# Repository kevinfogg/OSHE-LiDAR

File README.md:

# OSHE-LiDAR
This is the Open Source Hardware Enterprise (OSHE) LiDAR Bot repository at MTU

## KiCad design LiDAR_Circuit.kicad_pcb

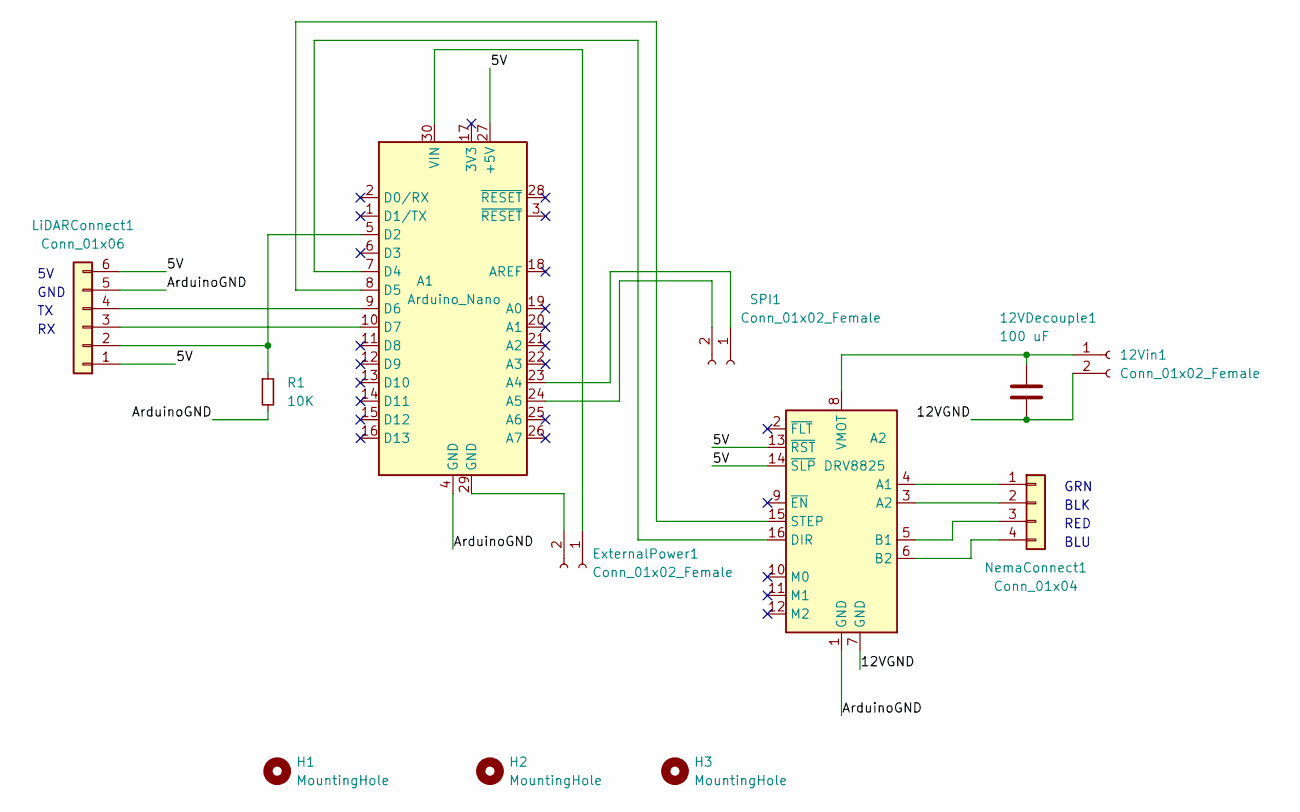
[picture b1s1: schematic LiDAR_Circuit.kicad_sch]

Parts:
12VDecouple1: 100 uF; CP_Radial_D6.3mm_P2.50mm
12Vin1: Conn_01x02_Female; TerminalBlock_Altech_AK300-2_P5.00mm
A1: Arduino_Nano
A2: DRV8825; Pololu_Breakout-16_15.2x20.3mm
ExternalPower1: Conn_01x02_Female; PinHeader_1x02_P2.54mm_Horizontal
H1, H2, H3: MountingHole; MountingHole_3.2mm_M3
LiDARConnect1: Conn_01x06; PinSocket_1x06_P2.54mm_Vertical
NemaConnect1: Conn_01x04; PinSocket_1x04_P2.54mm_Vertical
R1: 10K; R_Axial_DIN0204_L3.6mm_D1.6mm_P7.62mm_Horizontal
SPI1: Conn_01x02_Female; PinHeader_1x02_P2.54mm_Horizontal

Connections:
/5V: A1.27 (+5V), A2.13 (~RST), A2.14 (~SLP), LiDARConnect1.1, LiDARConnect1.6
/12VGND: 12VDecouple1.2, 12Vin1.2, A2.7 (GND)
/ArduinoGND: A1.4 (GND), A2.1 (GND), LiDARConnect1.5, R1.2
unnamed: 12VDecouple1.1, 12Vin1.1, A2.8 (VMOT)
unnamed: A1.5 (D2), LiDARConnect1.2, R1.1
unnamed: A1.7 (D4), A2.16 (DIR)
unnamed: A1.8 (D5), A2.15 (STEP)
unnamed: A1.9 (D6), LiDARConnect1.4
unnamed: A1.10 (D7), LiDARConnect1.3
unnamed: A1.29 (GND), ExternalPower1.2
unnamed: A1.30 (VIN), ExternalPower1.1
unnamed: A2.3 (A2), NemaConnect1.2
unnamed: A2.4 (A1), NemaConnect1.1
unnamed: A2.5 (B1), NemaConnect1.3
unnamed: A2.6 (B2), NemaConnect1.4
unnamed: A1.23 (A4), SPI1.1
unnamed: A1.24 (A5), SPI1.2

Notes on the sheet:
BLK
BLU
RED
GRN
GND

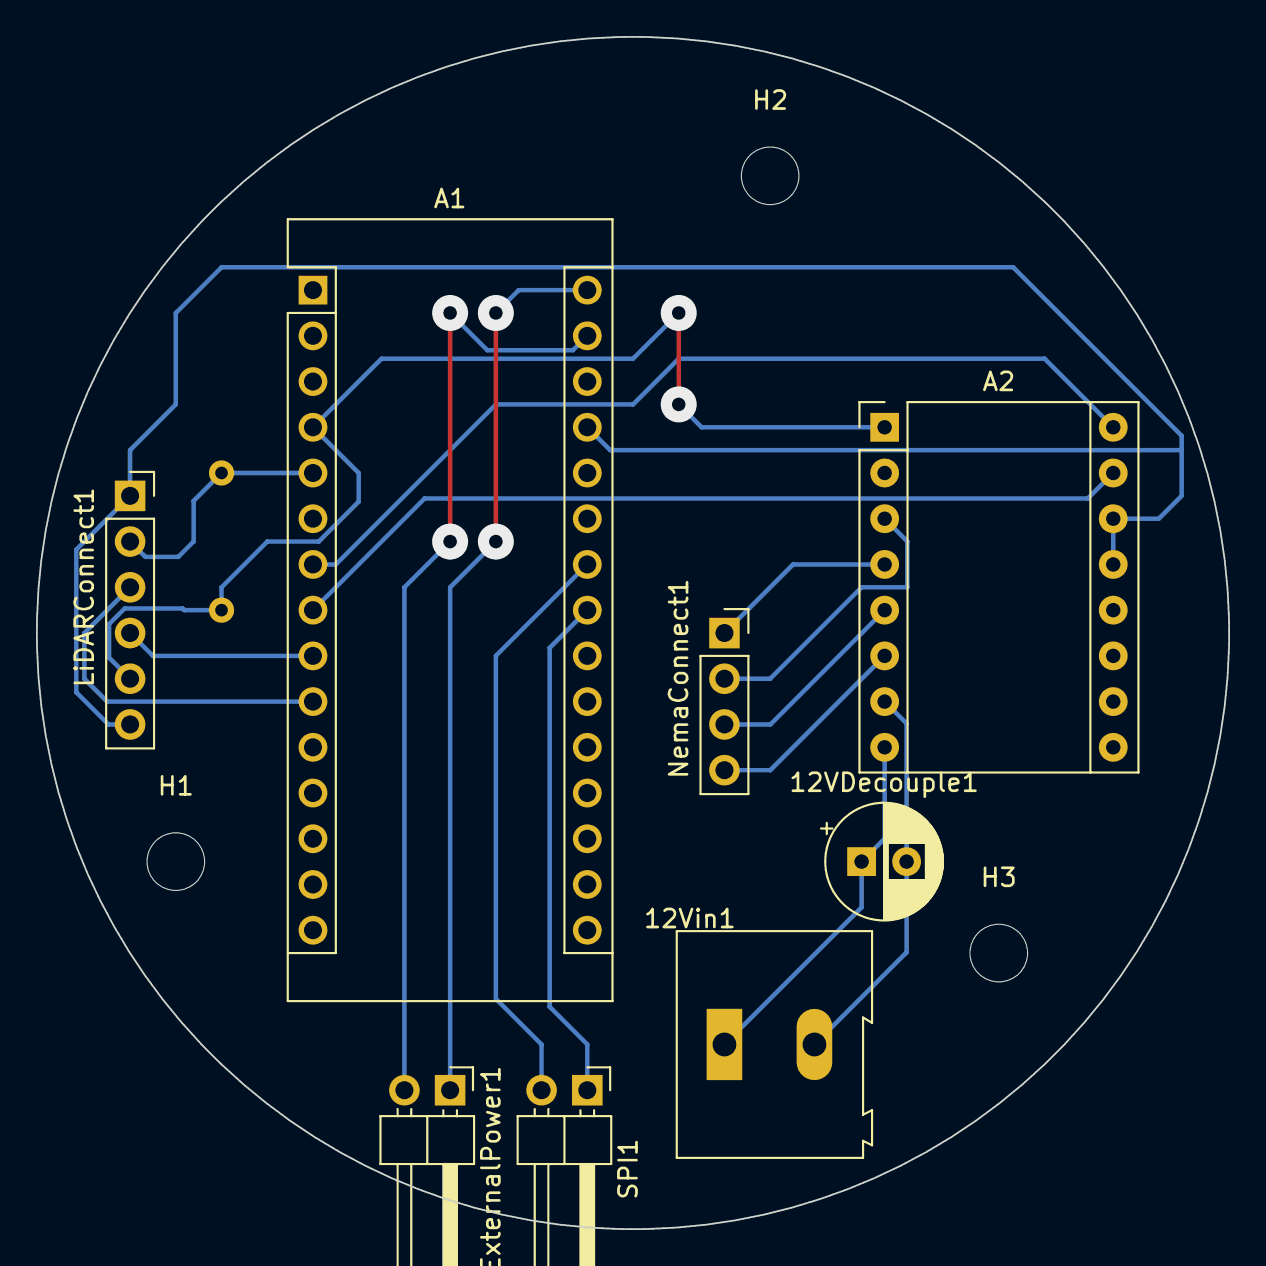
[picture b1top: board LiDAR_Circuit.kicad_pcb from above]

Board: 2 copper layers, 66.2 x 66.2 mm, 12 parts (1 on the bottom side), 17 nets.

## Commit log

2022-04-27 Add files via upload
    Here are the Freecad Files for this project. These files can be edited to suit the needs of a custom application of this project.
2022-04-27 Add files via upload
    Here are the STL files that can be sliced for printing. The frame has been included as 2 parts for convince as our Prusa i3 Mk 2 had problems printing the it as a single part.
